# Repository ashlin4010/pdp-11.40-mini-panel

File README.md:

# PDP-11/40 Mini Panel (Unfinished)

Included in this repository are the PCB files to make a miniature PDP-11/40 front panel. The board uses a XIAO nrf52840 dev board. No software has been written yet.

# Ordering pcbs
This project consists of three pcbs:
- A faceplate - Decorative only
    - pdp-11-colour.zip
    - 2 layers
    - PCB Color: White
    - Silkscreen Technology: EasyEDA multi-color silkscreen
- Main PCB - Has all electronics
    - pdp-11-pcb.zip
    - 4 layers
- Spacer PCB (Optional) - Removes the need for hot air
    - XIAO-nRF52840-spacer_thin.zip
    - 2 layers
    - Thickness: 0.8m
    - Deburring/Edge rounding: No

# Building
Place the spacer on the back of the nrf52840 module with the pads facing the the front. Solder the spacer to the back of the module using a minimal amount of solder. File the solder pints flat if needed.

Solder the module and spacer to the main PCB. Using some short wire solder the pads of the space to the main PCB. Skip the top most pad, its ground.

For the programming header orientation check [main pcb image](/images/pcb_back.jpg).

# Programming
¯\\_(ツ)_/¯

# BOM

| Quantity | Part                | Link                                                                                            |
|----------|---------------------|-------------------------------------------------------------------------------------------------|
| 1        | mini nrf52840       | https://www.aliexpress.com/item/1005008563470913.html                                           |
| 1        | 3.3V 1A SOT-223 Reg | https://www.digikey.co.nz/en/products/detail/texas-instruments/TLV1117LV33DCYR/2666508          |
| 40       | Red LED LSP47K      | https://www.digikey.co.nz/en/products/detail/ams-osram-usa-inc/LS-P47K-H1K2-1-0-2-R18-Z/1227985 |
| 2        | 1uf 0805            | https://www.digikey.co.nz/en/products/detail/samsung-electro-mechanics/CL21B105KAFNNNE/3886724  |
| 5        | 74HC595PW           | https://www.digikey.co.nz/en/products/detail/nexperia-usa-inc/74HC595PW-118/946653              |
| 40       | 150R 0805           | https://www.digikey.co.nz/en/products/detail/yageo/RC0805JR-07150RL/728255                      |
| 2        | 100R 0805           | https://www.digikey.co.nz/en/products/detail/yageo/RC0805JR-10100RL/14286702                    |
| 1        | Programming Header  | https://www.digikey.co.nz/en/products/detail/adafruit-industries-llc/4048/9843412               |
| 1        | Expansion Header    | https://www.digikey.co.nz/en/products/detail/adam-tech/HRS-2C-16-G-SMT-P/10245144               |

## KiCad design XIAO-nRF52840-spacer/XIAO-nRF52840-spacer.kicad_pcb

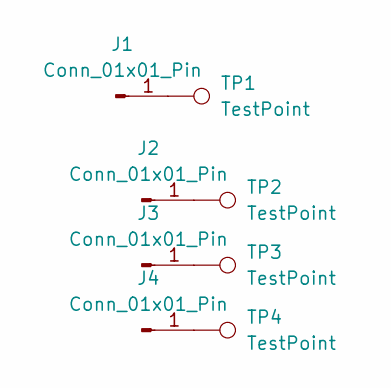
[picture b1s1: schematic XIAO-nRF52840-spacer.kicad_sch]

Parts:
J1, J2, J3, J4: Conn_01x01_Pin; PinHole
TP1, TP2, TP3, TP4: TestPoint; TestPoint_Pad_D1.0mm

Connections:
unnamed: J1.1, TP1.1
unnamed: J2.1, TP2.1
unnamed: J3.1, TP3.1
unnamed: J4.1, TP4.1

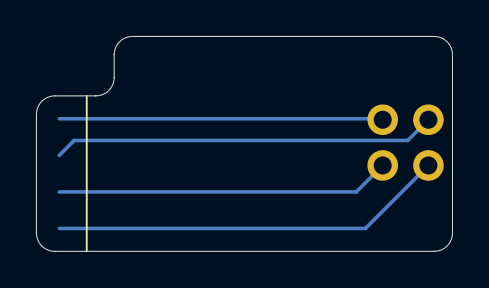
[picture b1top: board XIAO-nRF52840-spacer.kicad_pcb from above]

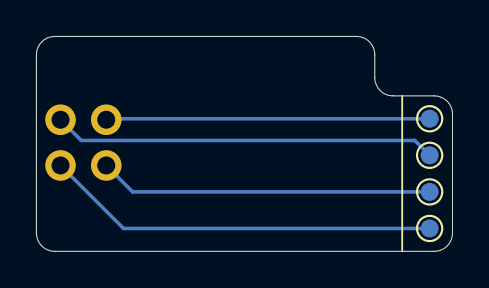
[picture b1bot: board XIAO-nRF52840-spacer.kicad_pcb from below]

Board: 2 copper layers, 23.1 x 11.9 mm, 8 parts (4 on the bottom side), 4 nets.

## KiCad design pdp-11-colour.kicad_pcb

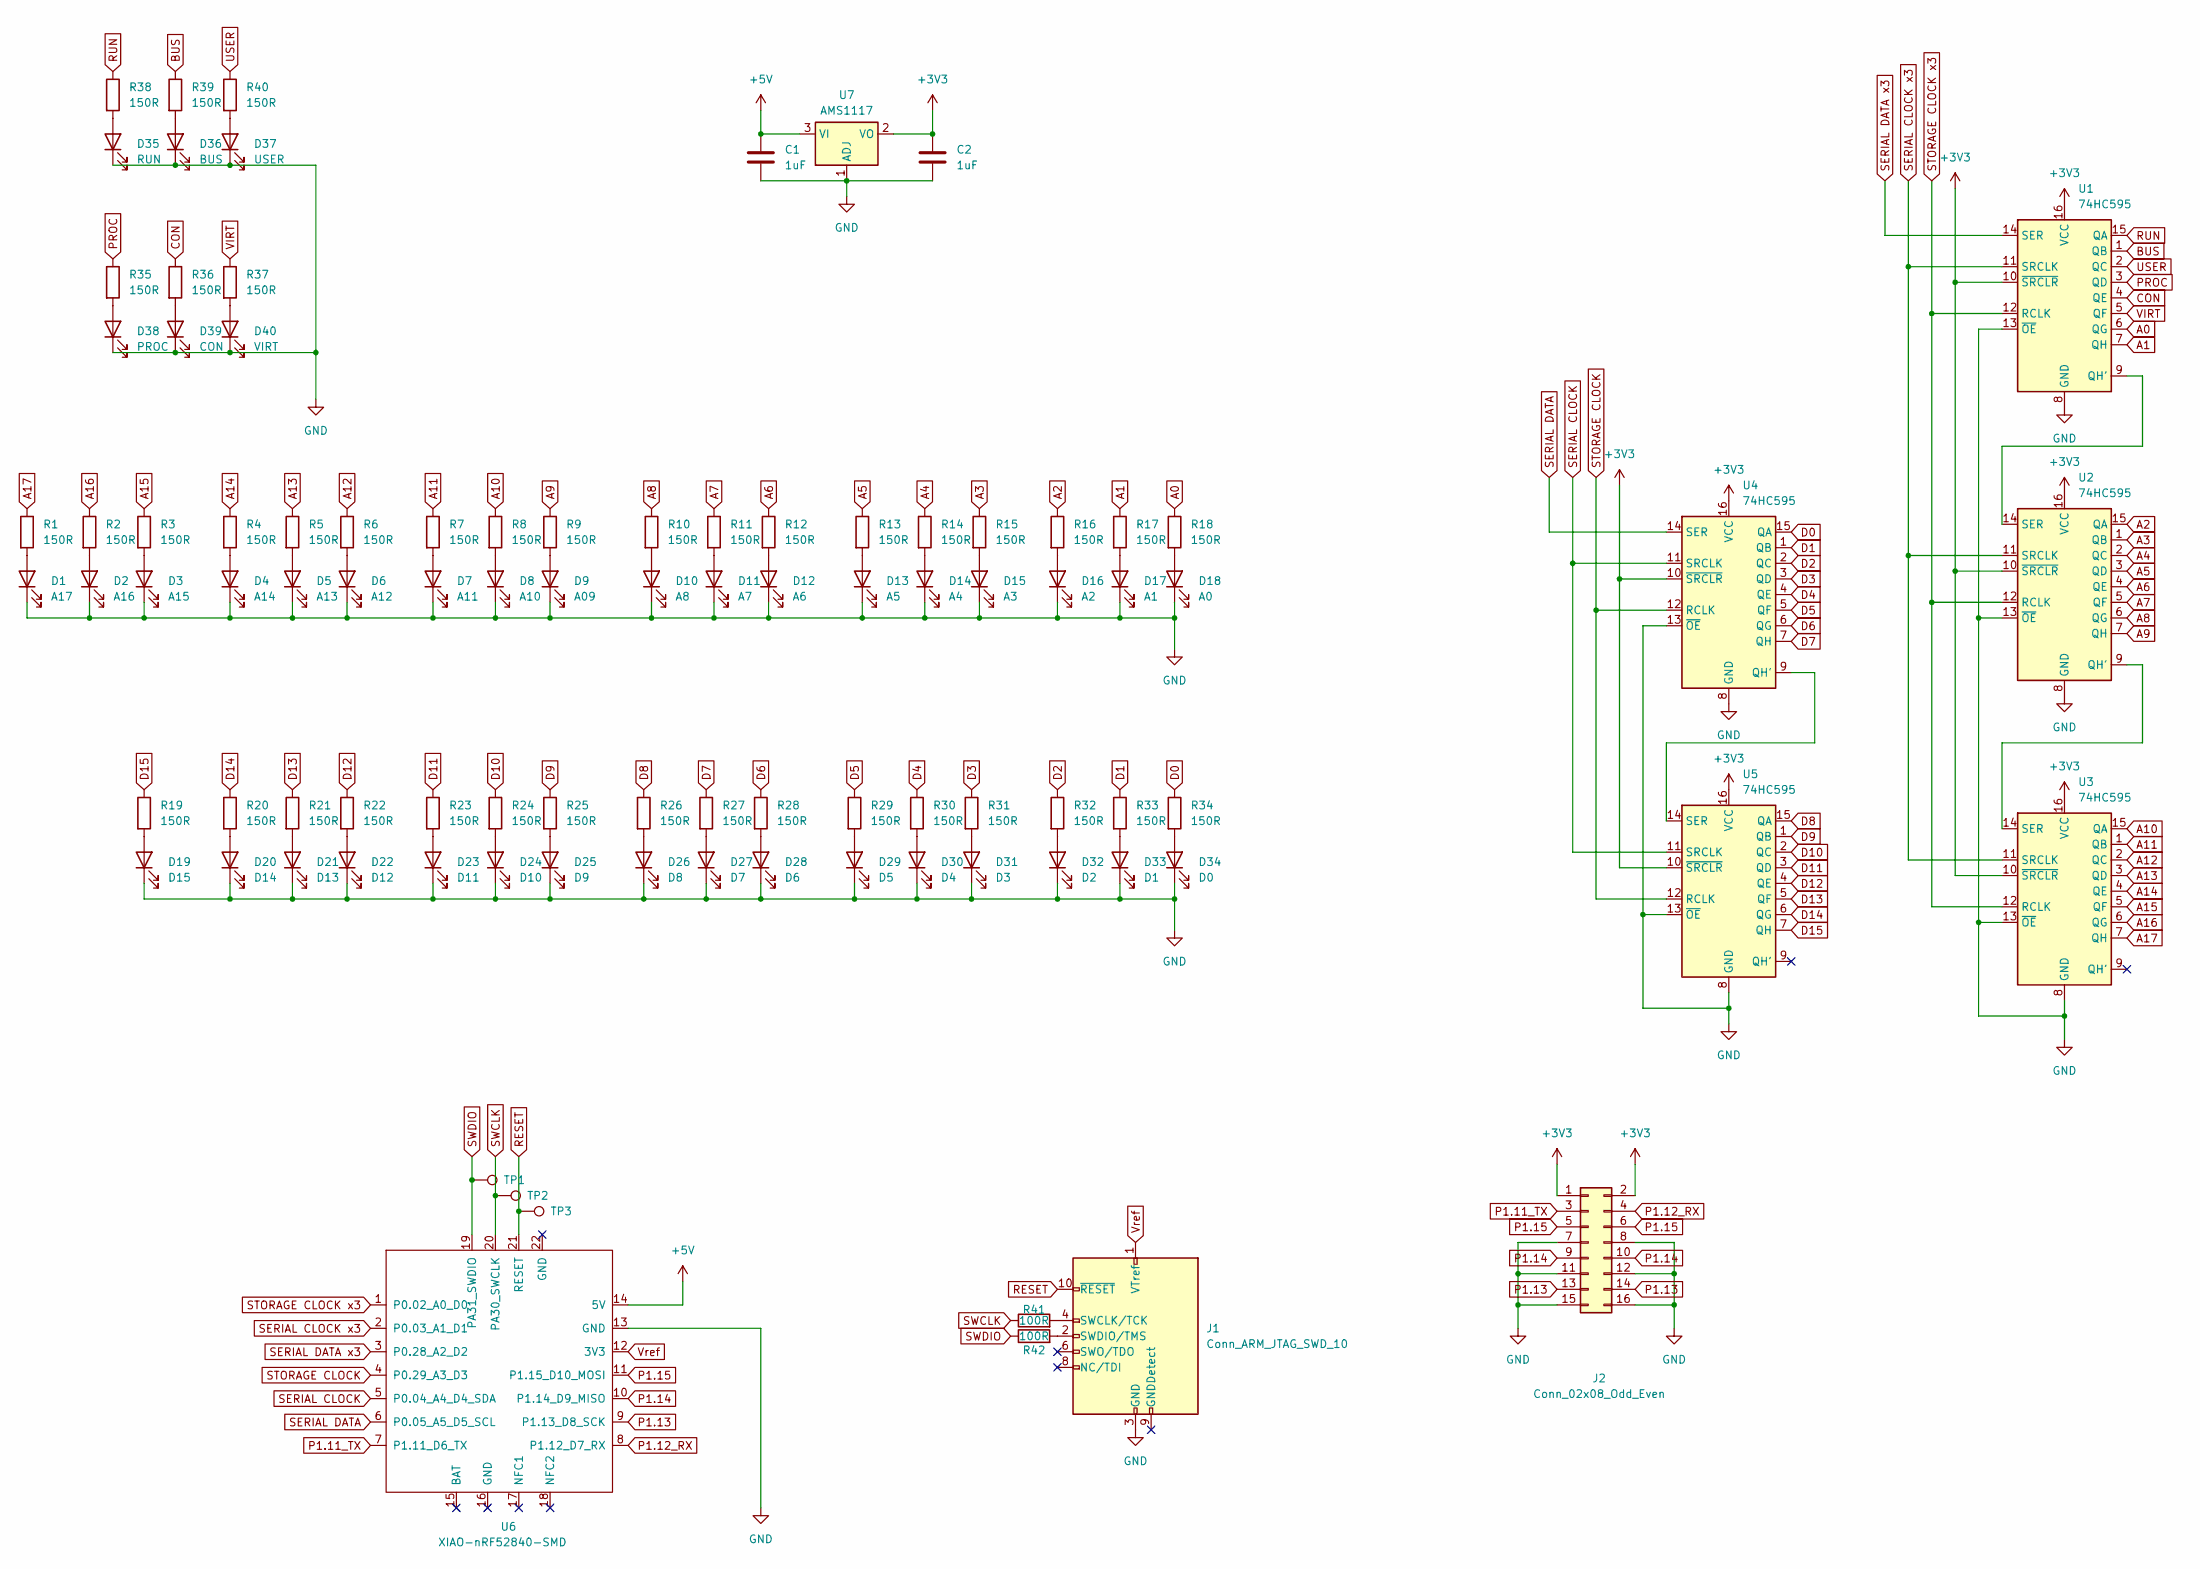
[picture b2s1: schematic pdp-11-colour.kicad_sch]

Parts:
C1, C2: 1uF; C_0805_2012Metric_Pad1.18x1.45mm_HandSolder
D1: A17; LED_Osram_Lx_P47F_D2mm_ReverseMount
D2: A16; LED_Osram_Lx_P47F_D2mm_ReverseMount
D3: A15; LED_Osram_Lx_P47F_D2mm_ReverseMount
D4: A14; LED_Osram_Lx_P47F_D2mm_ReverseMount
D5: A13; LED_Osram_Lx_P47F_D2mm_ReverseMount
D6: A12; LED_Osram_Lx_P47F_D2mm_ReverseMount
D7: A11; LED_Osram_Lx_P47F_D2mm_ReverseMount
D8: A10; LED_Osram_Lx_P47F_D2mm_ReverseMount
D9: A09; LED_Osram_Lx_P47F_D2mm_ReverseMount
D10: A8; LED_Osram_Lx_P47F_D2mm_ReverseMount
D11: A7; LED_Osram_Lx_P47F_D2mm_ReverseMount
D12: A6; LED_Osram_Lx_P47F_D2mm_ReverseMount
D13: A5; LED_Osram_Lx_P47F_D2mm_ReverseMount
D14: A4; LED_Osram_Lx_P47F_D2mm_ReverseMount
D15: A3; LED_Osram_Lx_P47F_D2mm_ReverseMount
D16: A2; LED_Osram_Lx_P47F_D2mm_ReverseMount
D17: A1; LED_Osram_Lx_P47F_D2mm_ReverseMount
D18: A0; LED_Osram_Lx_P47F_D2mm_ReverseMount
D19: D15; LED_Osram_Lx_P47F_D2mm_ReverseMount
D20: D14; LED_Osram_Lx_P47F_D2mm_ReverseMount
D21: D13; LED_Osram_Lx_P47F_D2mm_ReverseMount
D22: D12; LED_Osram_Lx_P47F_D2mm_ReverseMount
D23: D11; LED_Osram_Lx_P47F_D2mm_ReverseMount
D24: D10; LED_Osram_Lx_P47F_D2mm_ReverseMount
D25: D9; LED_Osram_Lx_P47F_D2mm_ReverseMount
D26: D8; LED_Osram_Lx_P47F_D2mm_ReverseMount
D27: D7; LED_Osram_Lx_P47F_D2mm_ReverseMount
D28: D6; LED_Osram_Lx_P47F_D2mm_ReverseMount
D29: D5; LED_Osram_Lx_P47F_D2mm_ReverseMount
D30: D4; LED_Osram_Lx_P47F_D2mm_ReverseMount
D31: D3; LED_Osram_Lx_P47F_D2mm_ReverseMount
D32: D2; LED_Osram_Lx_P47F_D2mm_ReverseMount
D33: D1; LED_Osram_Lx_P47F_D2mm_ReverseMount
D34: D0; LED_Osram_Lx_P47F_D2mm_ReverseMount
D35: RUN; LED_Osram_Lx_P47F_D2mm_ReverseMount
D36: BUS; LED_Osram_Lx_P47F_D2mm_ReverseMount
D37: USER; LED_Osram_Lx_P47F_D2mm_ReverseMount
D38: PROC; LED_Osram_Lx_P47F_D2mm_ReverseMount
D39: CON; LED_Osram_Lx_P47F_D2mm_ReverseMount
D40: VIRT; LED_Osram_Lx_P47F_D2mm_ReverseMount
J1: Conn_ARM_JTAG_SWD_10; PinHeader_2x05_P1.27mm_Vertical_SMD
J2: Conn_02x08_Odd_Even; PinSocket_2x08_P1.27mm_Vertical_SMD
R1, R2, R3, R4, R5, R6, R7, R8, R9, R10, R11, R12, R13, R14, R15, R16, R17, R18, R19, R20, R21, R22, R23, R24, R25, R26, R27, R28, R29, R30, R31, R32, R33, R34, R35, R36, R37, R38, R39, R40: 150R; R_0805_2012Metric_Pad1.20x1.40mm_HandSolder
R41, R42: 100R; R_0805_2012Metric_Pad1.20x1.40mm_HandSolder
TP1, TP2, TP3: TestPoint; TestPoint_Pad_D1.0mm
U1, U2, U3, U4, U5: 74HC595; TSSOP-16_4.4x5mm_P0.65mm
U6: XIAO-nRF52840-SMD
U7: AMS1117; SOT-223-3_TabPin2

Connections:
+3V3: C2.1, J2.1, J2.2, U1.10 (~SRCLR), U1.16 (VCC), U2.10 (~SRCLR), U2.16 (VCC), U3.10 (~SRCLR), U3.16 (VCC), U4.10 (~SRCLR), U4.16 (VCC), U5.10 (~SRCLR), U5.16 (VCC), U7.2 (VO)
+5V: C1.1, U6.14 (5V), U7.3 (VI)
A0: R18.1, U1.6 (QG)
A1: R17.1, U1.7 (QH)
A2: R16.1, U2.15 (QA)
A3: R15.1, U2.1 (QB)
A4: R14.1, U2.2 (QC)
A5: R13.1, U2.3 (QD)
A6: R12.1, U2.4 (QE)
A7: R11.1, U2.5 (QF)
A8: R10.1, U2.6 (QG)
A9: R9.1, U2.7 (QH)
A10: R8.1, U3.15 (QA)
A11: R7.1, U3.1 (QB)
A12: R6.1, U3.2 (QC)
A13: R5.1, U3.3 (QD)
A14: R4.1, U3.4 (QE)
A15: R3.1, U3.5 (QF)
A16: R2.1, U3.6 (QG)
A17: R1.1, U3.7 (QH)
BUS: R39.1, U1.1 (QB)
CON: R36.1, U1.4 (QE)
D0: R34.1, U4.15 (QA)
D1: R33.1, U4.1 (QB)
D2: R32.1, U4.2 (QC)
D3: R31.1, U4.3 (QD)
D4: R30.1, U4.4 (QE)
D5: R29.1, U4.5 (QF)
D6: R28.1, U4.6 (QG)
D7: R27.1, U4.7 (QH)
D8: R26.1, U5.15 (QA)
D9: R25.1, U5.1 (QB)
D10: R24.1, U5.2 (QC)
D11: R23.1, U5.3 (QD)
D12: R22.1, U5.4 (QE)
D13: R21.1, U5.5 (QF)
D14: R20.1, U5.6 (QG)
D15: R19.1, U5.7 (QH)
GND: C1.2, C2.2, D1.1 (K), D2.1 (K), D3.1 (K), D4.1 (K), D5.1 (K), D6.1 (K), D7.1 (K), D8.1 (K), D9.1 (K), D10.1 (K), D11.1 (K), D12.1 (K), D13.1 (K), D14.1 (K), D15.1 (K), D16.1 (K), D17.1 (K), D18.1 (K), D19.1 (K), D20.1 (K), D21.1 (K), D22.1 (K), D23.1 (K), D24.1 (K), D25.1 (K), D26.1 (K), D27.1 (K), D28.1 (K), D29.1 (K), D30.1 (K), D31.1 (K), D32.1 (K), D33.1 (K), D34.1 (K), D35.1 (K), D36.1 (K), D37.1 (K), D38.1 (K), D39.1 (K), D40.1 (K), J1.3 (GND), J1.5 (GND), J2.7, J2.8, J2.11, J2.12, J2.15, J2.16, U1.8 (GND), U1.13 (~OE), U2.8 (GND), U2.13 (~OE), U3.8 (GND), U3.13 (~OE), U4.8 (GND), U4.13 (~OE), U5.8 (GND), U5.13 (~OE), U6.13 (GND), U7.1 (ADJ)
unnamed: D1.2 (A), R1.2
unnamed: D2.2 (A), R2.2
unnamed: D3.2 (A), R3.2
unnamed: D4.2 (A), R4.2
unnamed: D5.2 (A), R5.2
unnamed: D6.2 (A), R6.2
unnamed: D7.2 (A), R7.2
unnamed: D8.2 (A), R8.2
unnamed: D9.2 (A), R9.2
unnamed: D10.2 (A), R10.2
unnamed: D11.2 (A), R11.2
unnamed: D12.2 (A), R12.2
unnamed: D13.2 (A), R13.2
unnamed: D14.2 (A), R14.2
unnamed: D15.2 (A), R15.2
unnamed: D16.2 (A), R16.2
unnamed: D17.2 (A), R17.2
unnamed: D18.2 (A), R18.2
unnamed: D19.2 (A), R19.2
unnamed: D20.2 (A), R20.2
unnamed: D21.2 (A), R21.2
unnamed: D22.2 (A), R22.2
unnamed: D23.2 (A), R23.2
unnamed: D24.2 (A), R24.2
unnamed: D25.2 (A), R25.2
unnamed: D26.2 (A), R26.2
unnamed: D27.2 (A), R27.2
unnamed: D28.2 (A), R28.2
unnamed: D29.2 (A), R29.2
unnamed: D30.2 (A), R30.2
unnamed: D31.2 (A), R31.2
unnamed: D32.2 (A), R32.2
unnamed: D33.2 (A), R33.2
unnamed: D34.2 (A), R34.2
unnamed: D35.2 (A), R38.2
unnamed: D36.2 (A), R39.2
unnamed: D37.2 (A), R40.2
unnamed: D38.2 (A), R35.2
unnamed: D39.2 (A), R36.2
unnamed: D40.2 (A), R37.2
unnamed: J1.4 (SWCLK/TCK), R41.2
unnamed: J1.2 (SWDIO/TMS), R42.2
unnamed: U1.9 (QH'), U2.14 (SER)
unnamed: U2.9 (QH'), U3.14 (SER)
unnamed: U4.9 (QH'), U5.14 (SER)
P1.11_TX: J2.3, U6.7 (P1.11_D6_TX)
P1.12_RX: J2.4, U6.8 (P1.12_D7_RX)
P1.13: J2.13, J2.14, U6.9 (P1.13_D8_SCK)
P1.14: J2.9, J2.10, U6.10 (P1.14_D9_MISO)
P1.15: J2.5, J2.6, U6.11 (P1.15_D10_MOSI)
PROC: R35.1, U1.3 (QD)
RESET: J1.10 (~RESET), TP3.1, U6.21 (RESET)
RUN: R38.1, U1.15 (QA)
SERIAL CLOCK: U4.11 (SRCLK), U5.11 (SRCLK), U6.5 (P0.04_A4_D4_SDA)
SERIAL CLOCK x3: U1.11 (SRCLK), U2.11 (SRCLK), U3.11 (SRCLK), U6.2 (P0.03_A1_D1)
SERIAL DATA: U4.14 (SER), U6.6 (P0.05_A5_D5_SCL)
SERIAL DATA x3: U1.14 (SER), U6.3 (P0.28_A2_D2)
STORAGE CLOCK: U4.12 (RCLK), U5.12 (RCLK), U6.4 (P0.29_A3_D3)
STORAGE CLOCK x3: U1.12 (RCLK), U2.12 (RCLK), U3.12 (RCLK), U6.1 (P0.02_A0_D0)
SWCLK: R41.1, TP2.1, U6.20 (PA30_SWCLK)
SWDIO: R42.1, TP1.1, U6.19 (PA31_SWDIO)
USER: R40.1, U1.2 (QC)
VIRT: R37.1, U1.5 (QF)
Vref: J1.1 (VTref), U6.12 (3V3)

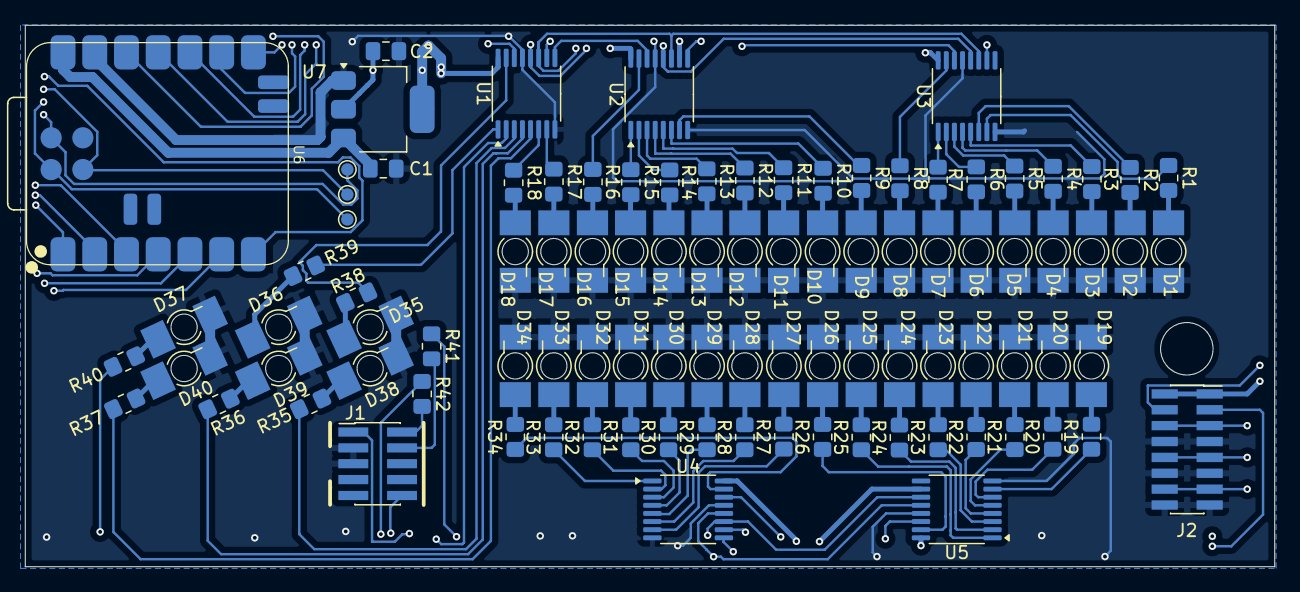
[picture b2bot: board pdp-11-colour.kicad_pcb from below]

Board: 4 copper layers, 100.0 x 43.3 mm, 96 parts (96 on the bottom side), 103 nets.

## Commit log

2025-06-29 Added PCB files
2025-06-29 Added readme
